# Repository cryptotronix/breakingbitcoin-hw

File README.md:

# BB-Hardware
Breaking Bitcoin Hardware

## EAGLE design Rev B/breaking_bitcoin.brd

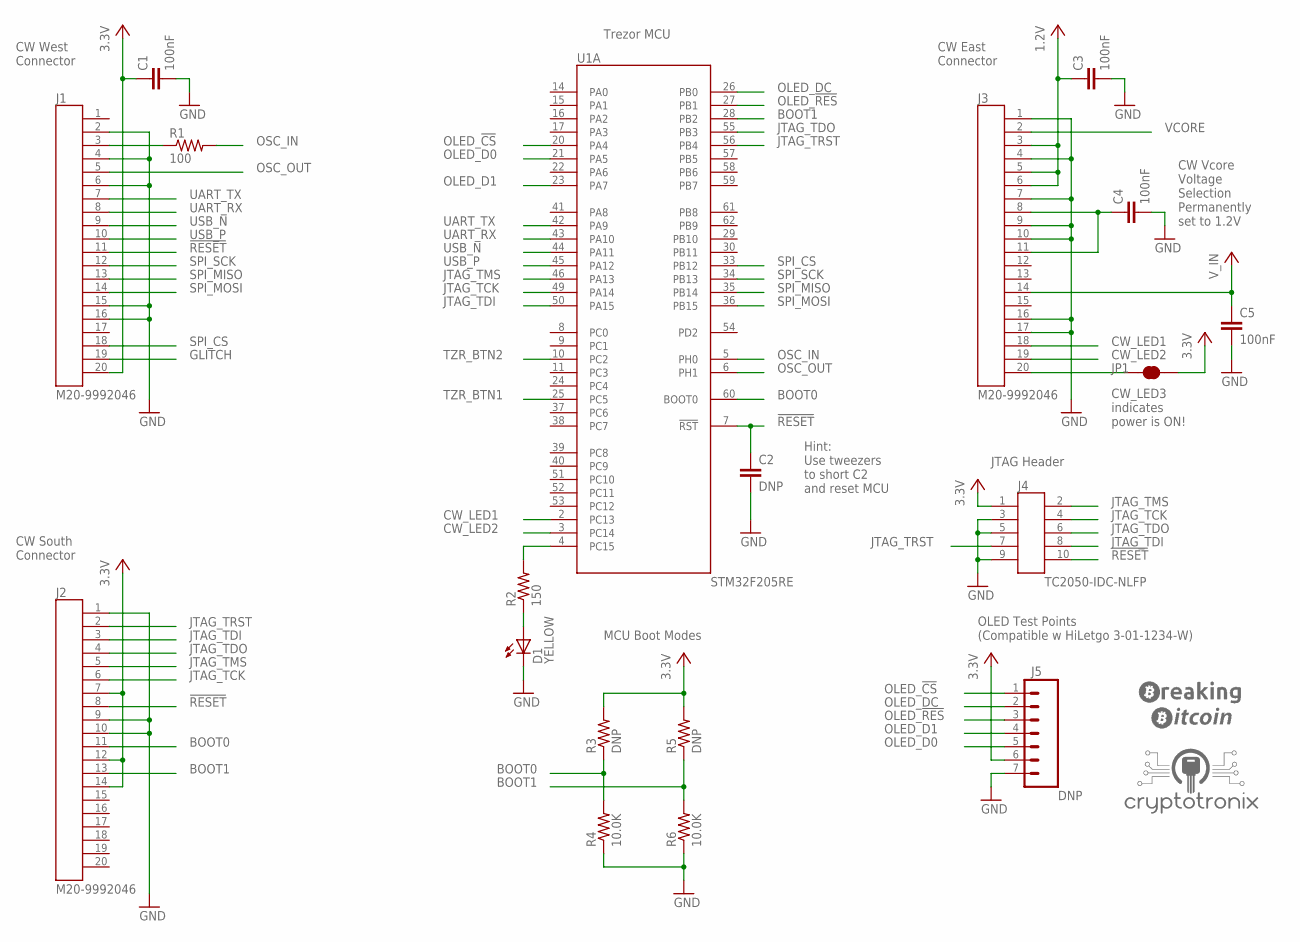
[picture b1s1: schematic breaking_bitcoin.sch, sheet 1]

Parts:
C1, C3, C4, C5: 100nF; C0603
C2: DNP; C0603
D1: YELLOW; 0603
J1, J2, J3: M20-9992046
J4: TC2050-IDC-NLFP
J5: DNP; 1X07
JP1: JUMPER-PAD-2-NC_BY_TRACE; PAD-JUMPER-2-NC_BY_TRACE_YES_SILK
R1: 100; R0603
R2: 150; R0603
R3, R5: DNP; R0603
R4, R6: 10.0K; R0603
U1: STM32F205RE; LQFP64
U$1: BB_LOGO
U$2: CRYPTOTRONIX_LOGO

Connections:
0V: C1.2, C2.2, C3.2, C4.2, C5.2, D1.C, J1.2, J1.4, J1.6, J1.15, J1.16, J2.1, J2.9, J2.10, J3.1, J3.4, J3.7, J3.9, J3.10, J3.16, J3.17, J4.3, J4.5, J4.9, J5.7, R4.1, R6.1; also elsewhere on the board
1.2V: C3.1, J3.3, J3.5, J3.6; also elsewhere on the board
3.3V: C1.1, J1.20, J2.7, J2.12, J2.14, J4.1, J5.6, JP1.2, R3.2, R5.2; also elsewhere on the board
!RESET: C2.1, J1.11, J2.8, J4.10, U1.7 (!RST)
BOOT0: J2.11, R3.1, R4.2, U1.60 (BOOT0)
BOOT1: J2.13, R5.1, R6.2, U1.28 (PB2)
CW_LED1: J3.18, U1.2 (PC13)
CW_LED2: J3.19, U1.3 (PC14)
GLITCH: J1.19; also elsewhere on the board
JTAG_TCK: J2.6, J4.4, U1.49 (PA14)
JTAG_TDI: J2.3, J4.8, U1.50 (PA15)
JTAG_TDO: J2.4, J4.6, U1.55 (PB3)
JTAG_TMS: J2.5, J4.2, U1.46 (PA13)
JTAG_TRST: J2.2, J4.7, U1.56 (PB4)
unnamed: J1.3, R1.1
unnamed: R2.2, U1.4 (PC15)
unnamed: C4.1, J3.8, J3.11
unnamed: D1.A, R2.1
unnamed: J3.20, JP1.1
OLED_!CS: J5.1, U1.20 (PA4); also elsewhere on the board
OLED_!RES: J5.3, U1.27 (PB1); also elsewhere on the board
OLED_D0: J5.5, U1.21 (PA5); also elsewhere on the board
OLED_D1: J5.4, U1.23 (PA7); also elsewhere on the board
OLED_DC: J5.2, U1.26 (PB0); also elsewhere on the board
OSC_IN: R1.2, U1.5 (PH0); also elsewhere on the board
OSC_OUT: J1.5, U1.6 (PH1); also elsewhere on the board
SPI_CS: J1.18, U1.33 (PB12)
SPI_MISO: J1.13, U1.35 (PB14)
SPI_MOSI: J1.14, U1.36 (PB15)
SPI_SCK: J1.12, U1.34 (PB13)
TZR_BTN1: U1.25 (PC5); also elsewhere on the board
TZR_BTN2: U1.10 (PC2); also elsewhere on the board
UART_RX: J1.8, U1.43 (PA10)
UART_TX: J1.7, U1.42 (PA9); also elsewhere on the board
USB_N: J1.9, U1.44 (PA11); also elsewhere on the board
USB_P: J1.10, U1.45 (PA12); also elsewhere on the board
VCORE: J3.2; also elsewhere on the board
V_IN: C5.1, J3.14; also elsewhere on the board

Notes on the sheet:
Trezor MCU
CW West Connector
CW South Connector
CW East Connector
JTAG Header
MCU Boot Modes
CW Vcore Voltage Selection Permanently set to 1.2V
CW_LED3 indicates power is ON!
OLED Test Points (Compatible w HiLetgo 3-01-1234-W)
Hint: Use tweezers to short C2 and reset MCU

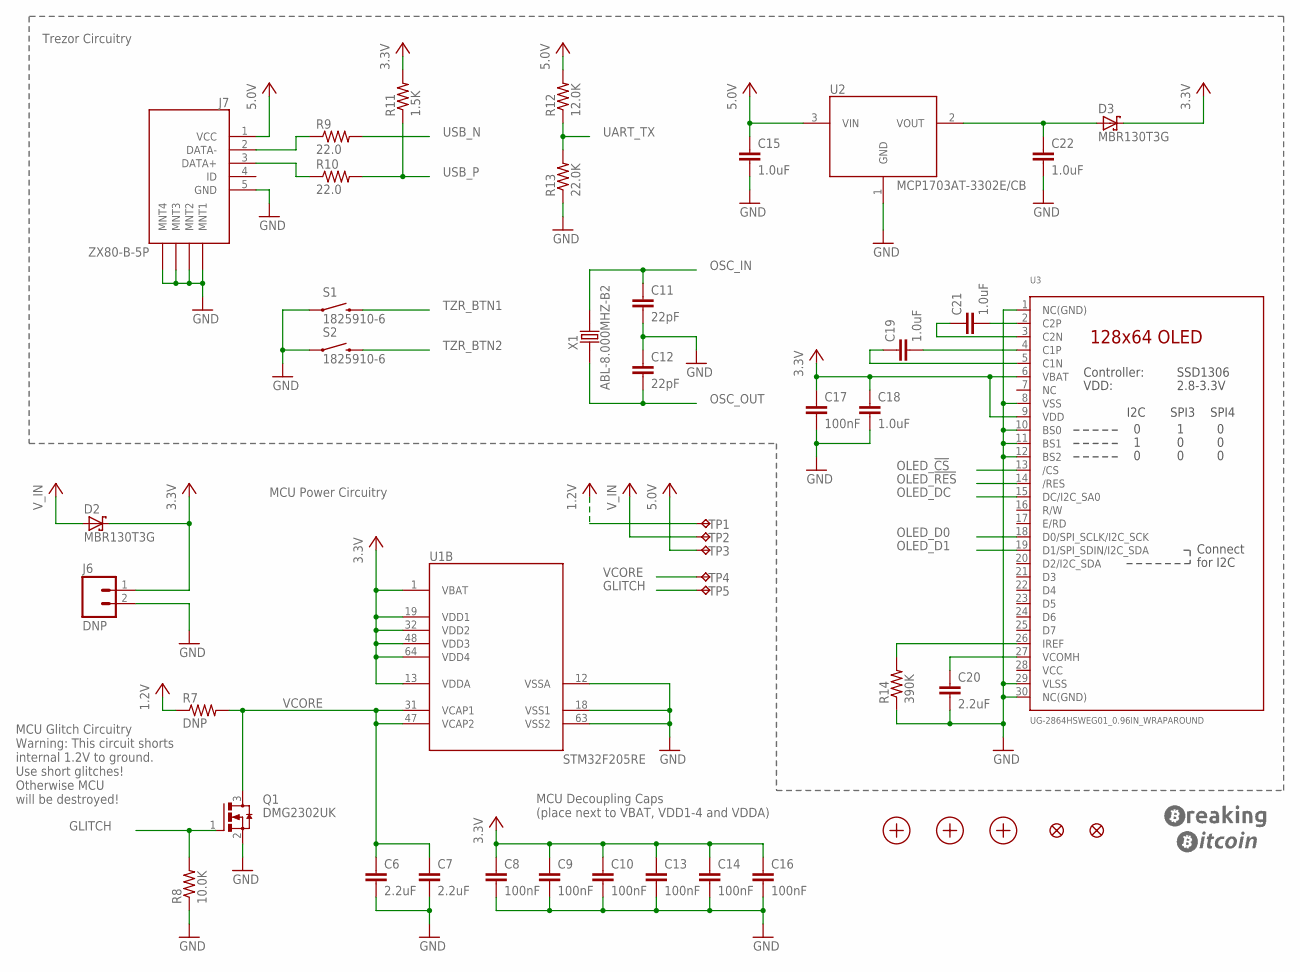
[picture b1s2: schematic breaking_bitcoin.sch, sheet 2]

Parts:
C6, C7, C20: 2.2uF; C0603
C8, C9, C10, C13, C14, C16, C17: 100nF; C0603
C11, C12: 22pF; C0603
C15, C18, C19, C21, C22: 1.0uF; C0603
D2, D3: MBR130T3G; SOD123
FD1, FD2: FIDUCIALUFIDUCIAL; MICRO-FIDUCIAL
J6: DNP; M20-9990246
J7: ZX80-B-5P
MNT1, MNT2, MNT3: MOUNT-HOLE-NO-PLATE4-40; MOUNT-HOLE-NO-PLATE-4-40
Q1: DMG2302UK
R7: DNP; R0603
R8: 10.0K; R0603
R9, R10: 22.0; R0603
R11: 1.5K; R0603
R12: 12.0K; R0603
R13: 22.0K; R0603
R14: 390K; R0603
S1, S2: 1825910-6; SWITCH-TACT-TH
TP1, TP2, TP3, TP4, TP5: TEST-POINT40MIL; TEST-POINT-40MILL
U1: STM32F205RE; LQFP64
U2: MCP1703AT-3302E/CB
U3: UG-2864HSWEG01_0.96IN_WRAPAROUND
U$3: BB_LOGO
X1: ABL-8.000MHZ-B2

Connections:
0V: C6.2, C7.2, C8.2, C9.2, C10.2, C11.2, C12.1, C13.2, C14.2, C15.2, C16.2, C17.2, C18.2, C20.2, C22.2, J6.2, J7.5 (GND), J7.M1 (MNT1), J7.M2 (MNT2), J7.M3 (MNT3), J7.M4 (MNT4), Q1.2 (S), R8.1, R13.1, R14.1, S1.1, S2.1, U1.12 (VSSA), U1.18 (VSS1), U1.63 (VSS2), U2.1 (GND), U3.1 (NC(GND)), U3.8 (VSS), U3.10 (BS0), U3.11 (BS1), U3.12 (BS2), U3.29 (VLSS), U3.30 (NC(GND)); also elsewhere on the board
1.2V: R7.1, TP1.1; also elsewhere on the board
3.3V: C8.1, C9.1, C10.1, C13.1, C14.1, C16.1, C17.1, C18.1, D2.C, D3.C, J6.1, R11.2, U1.1 (VBAT), U1.13 (VDDA), U1.19 (VDD1), U1.32 (VDD2), U1.48 (VDD3), U1.64 (VDD4), U3.6 (VBAT), U3.9 (VDD); also elsewhere on the board
5.0V: C15.1, J7.1 (VCC), R12.2, TP3.1, U2.3 (VIN)
GLITCH: Q1.1 (G), R8.2, TP5.1; also elsewhere on the board
unnamed: C19.1, U3.5 (C1N)
unnamed: C22.1, D3.A, U2.2 (VOUT)
unnamed: C19.2, U3.4 (C1P)
unnamed: C21.2, U3.2 (C2P)
unnamed: J7.2 (DATA-), R9.1
unnamed: J7.3 (DATA+), R10.1
unnamed: C21.1, U3.3 (C2N)
unnamed: C20.1, U3.27 (VCOMH)
unnamed: R14.2, U3.26 (IREF)
OLED_!CS: U3.13 (/CS); also elsewhere on the board
OLED_!RES: U3.14 (/RES); also elsewhere on the board
OLED_D0: U3.18 (D0/SPI_SCLK/I2C_SCK); also elsewhere on the board
OLED_D1: U3.19 (D1/SPI_SDIN/I2C_SDA); also elsewhere on the board
OLED_DC: U3.15 (DC/I2C_SA0); also elsewhere on the board
OSC_IN: C11.1, X1.2; also elsewhere on the board
OSC_OUT: C12.2, X1.1; also elsewhere on the board
TZR_BTN1: S1.3 (2); also elsewhere on the board
TZR_BTN2: S2.3 (2); also elsewhere on the board
UART_TX: R12.1, R13.2; also elsewhere on the board
USB_N: R9.2; also elsewhere on the board
USB_P: R10.2, R11.1; also elsewhere on the board
VCC: U3.28 (VCC)
VCORE: C6.1, C7.1, Q1.3 (D), R7.2, TP4.1, U1.31 (VCAP1), U1.47 (VCAP2); also elsewhere on the board
V_IN: D2.A, TP2.1; also elsewhere on the board

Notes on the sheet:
MCU Decoupling Caps (place next to VBAT, VDD1-4 and VDDA)
MCU Glitch Circuitry Warning: This circuit shorts internal 1.2V to ground. Use short glitches! Otherwise MCU will be destroyed!
MCU Power Circuitry
Trezor Circuitry

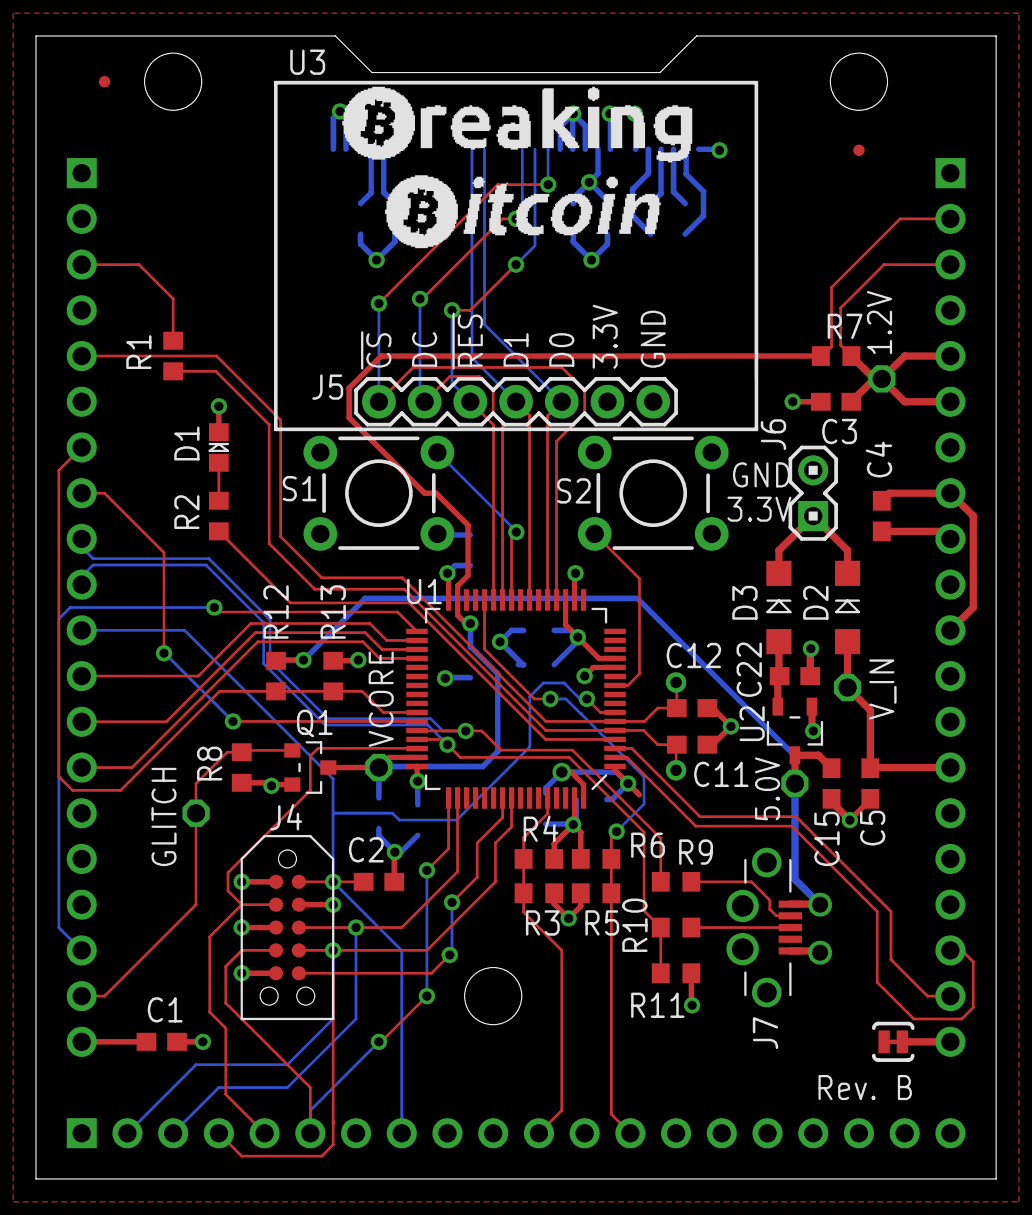
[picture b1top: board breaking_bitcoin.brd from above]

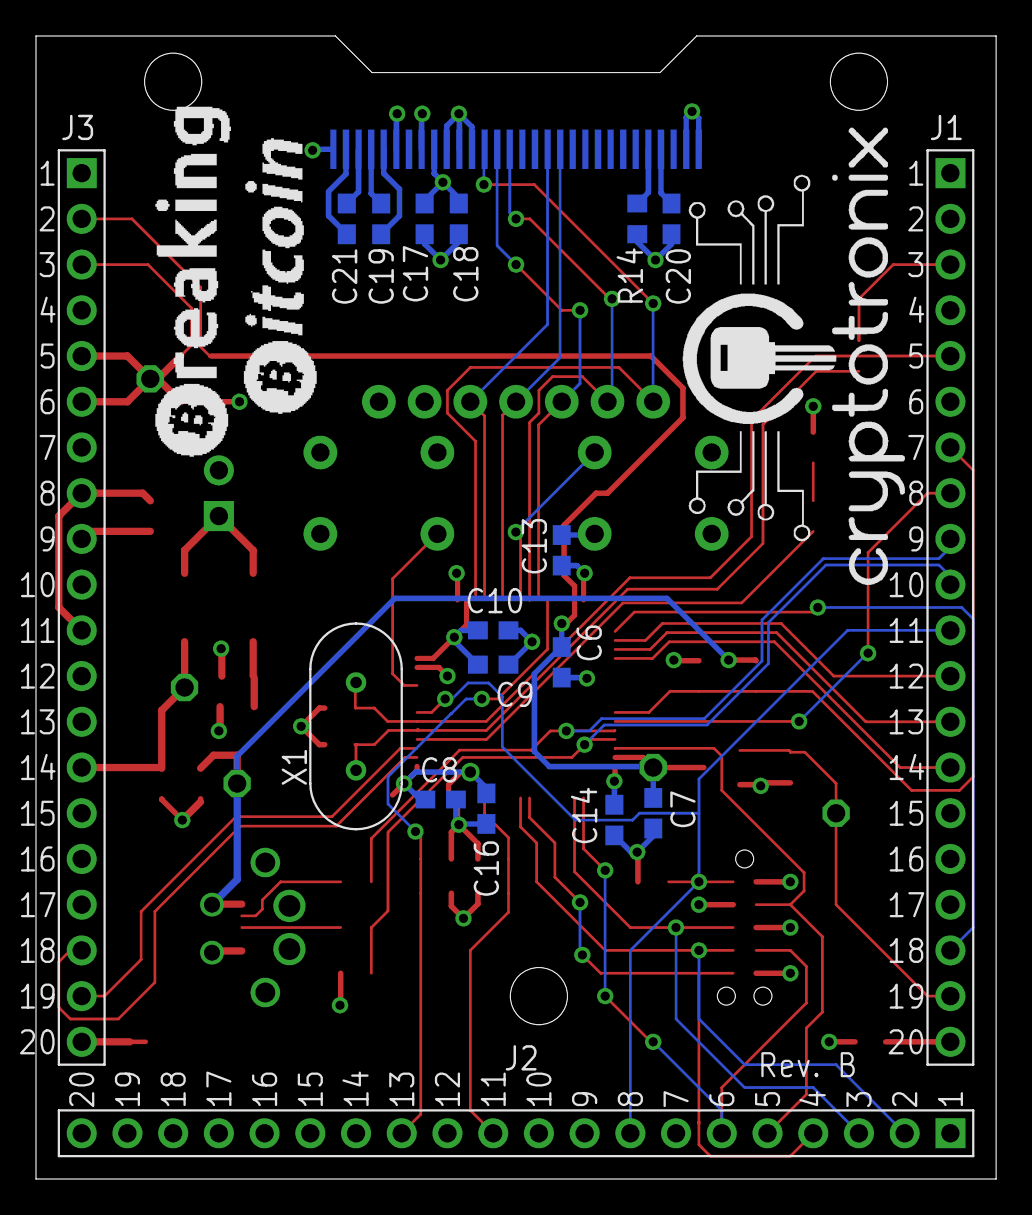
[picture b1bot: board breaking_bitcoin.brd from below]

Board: 2 copper layers, 53.3 x 63.5 mm, 67 parts (20 on the bottom side), 48 nets.

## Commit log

2017-06-23 Adding Rev. A of the Breaking Bitcoin board
2017-06-23 Adding BOM/Gerbers
2017-06-23 Updating silkscreen
2017-06-26 Improving 3.3V power plane
2017-06-26 Some cosmetic improvements to the schematic
2017-06-26 Adding read_me for the gerbers
2017-06-27 Removing drill holes marking OLED ffc edge
2017-06-28 Adding Rev. B. Fixing button mixup
2017-06-29 Fixing south bridge for the Rev. B
2017-07-08 Generating gerbers for Rev. B
2017-07-10 Rev. B BOM and CPL
2017-07-10 Updating CPL
2017-07-12 Adding reset MCU hint notes
2017-07-13 Changing all via sizes to 20mil
2017-07-13 Updating gitignore
2017-07-27 Adding BB Parts Kit
2017-07-27 BB Parts Kit 2

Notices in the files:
parts and their libraries:
microbuilder: This work is placed in the public domain, and may be freely used for commercial and non-commercial work with the following conditions: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
SparkFun-Connectors: Licensing: Creative Commons ShareAlike 4.0 International - https://creativecommons.org/licenses/by-sa/4.0
